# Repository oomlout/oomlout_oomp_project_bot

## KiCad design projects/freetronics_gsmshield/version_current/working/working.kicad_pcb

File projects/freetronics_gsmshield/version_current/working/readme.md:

# OOMP Project  
## GSMShield  by freetronics  
  
oomp key: oomp_projects_flat_freetronics_gsmshield  
(snippet of original readme)  

  full source readme at [readme_src.md](readme_src.md)  
  
source repo at: [https://github.com/freetronics/GSMShield](https://github.com/freetronics/GSMShield)  
## Board  

## Schematic  

[schematic pdf](working_schematic.pdf)  
## Images

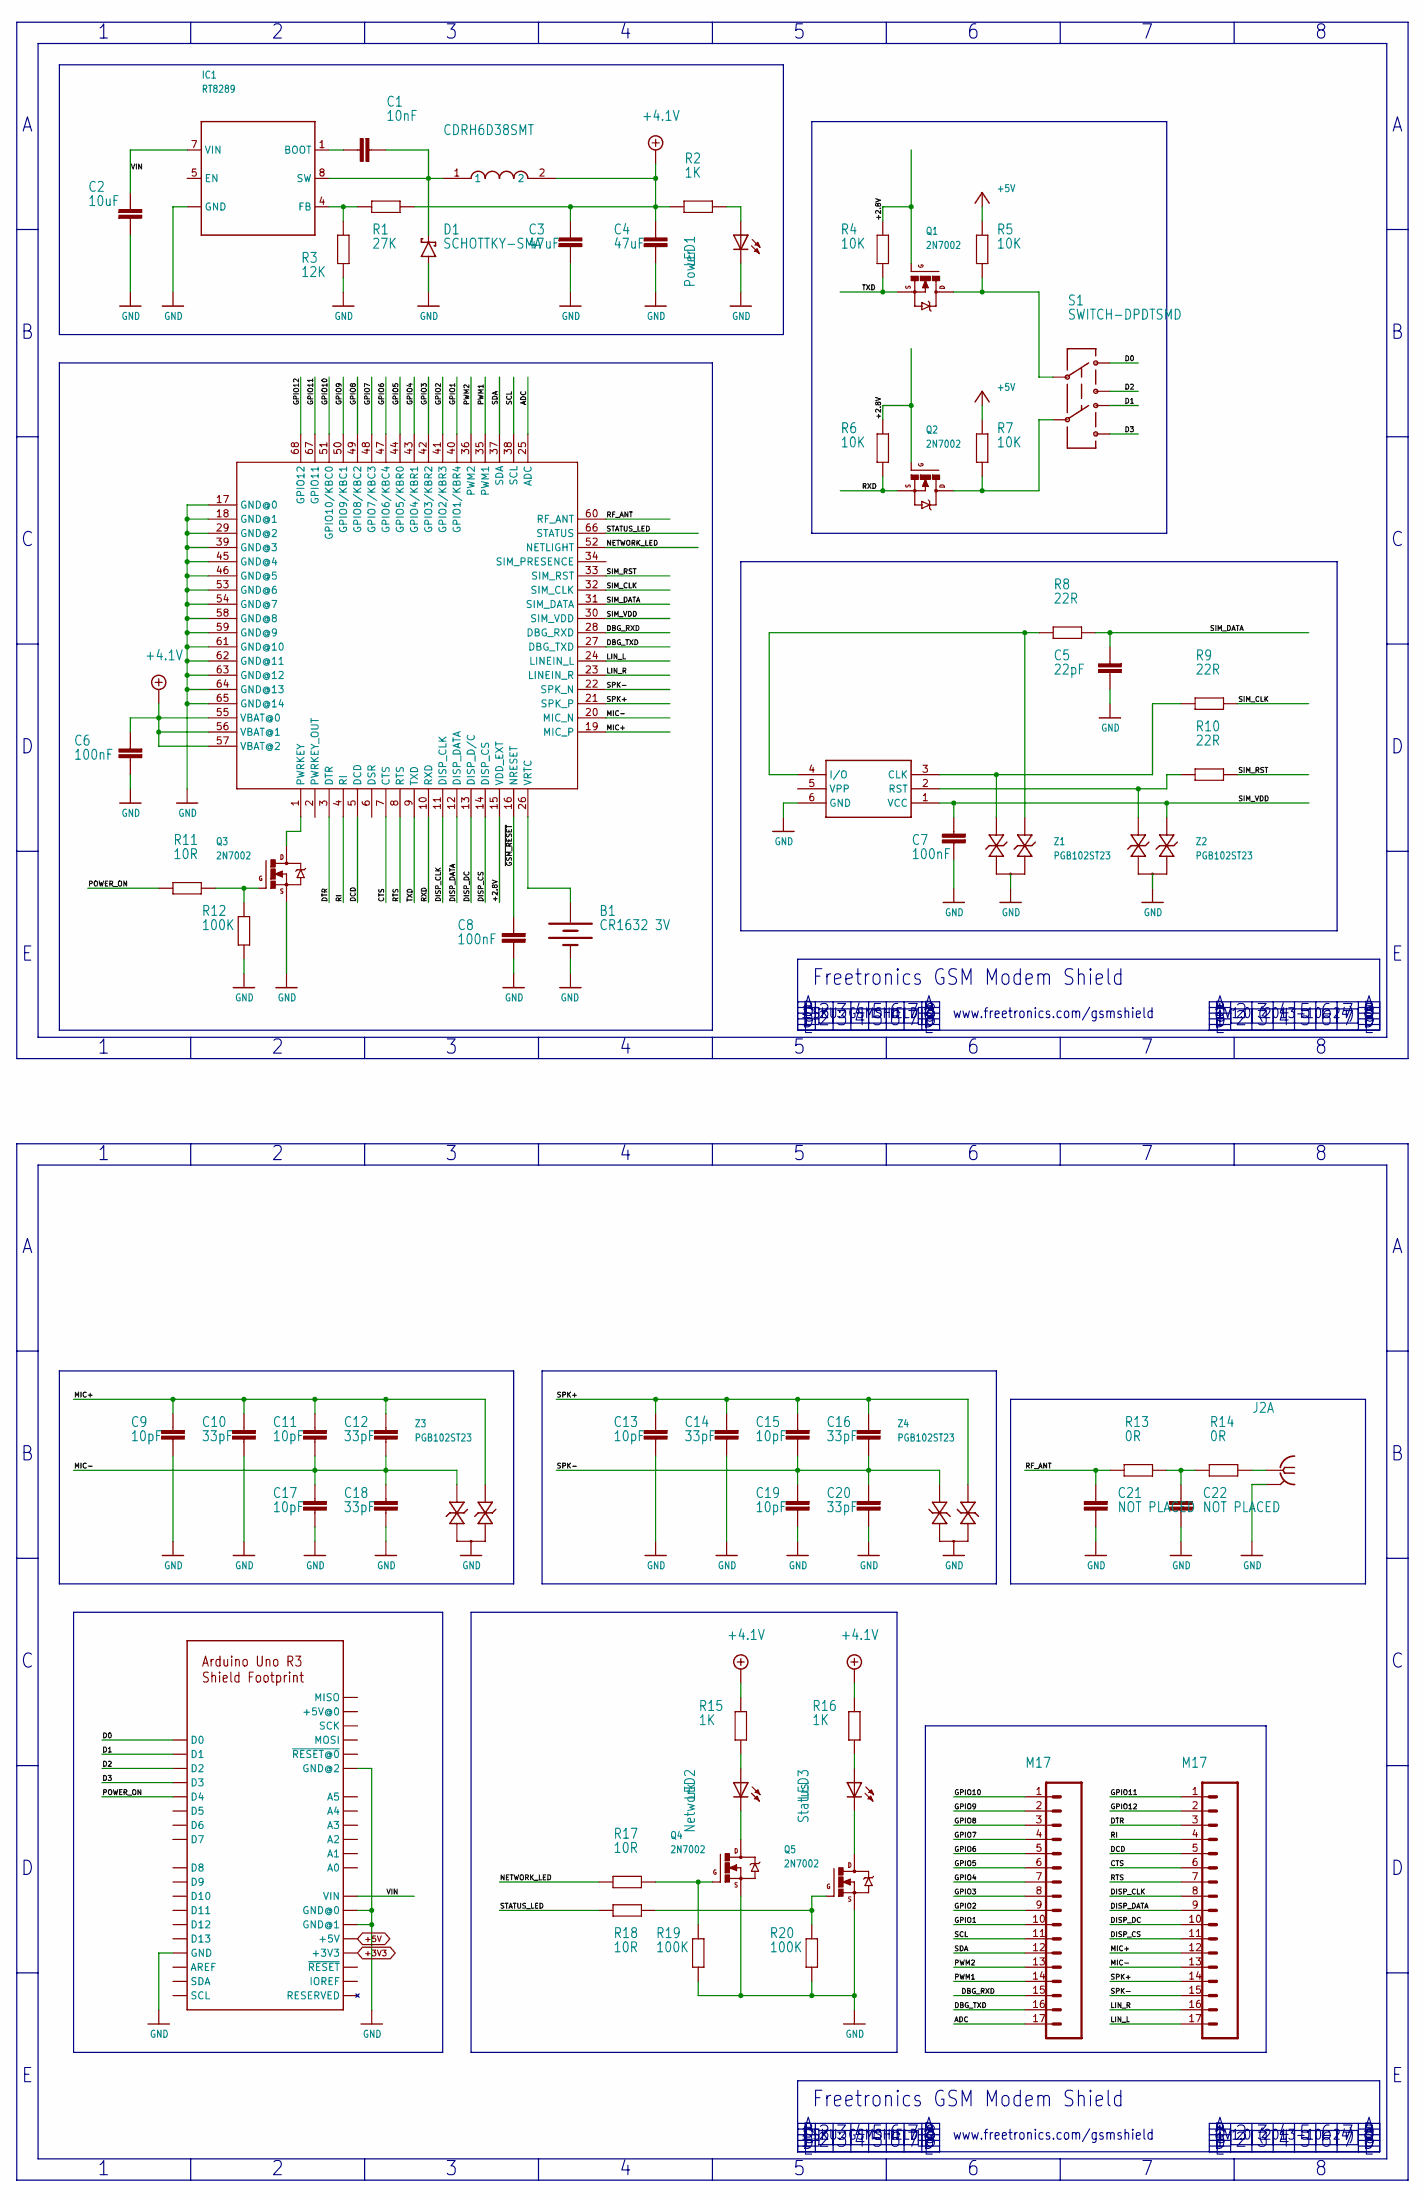
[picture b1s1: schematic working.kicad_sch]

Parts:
B1: CR1632 3V; BATCON_16MM
C1: 10nF; 0603
C2: 10uF; C1206; VOLTAGE 35V
C3, C4: 47uF; C1206; VOLTAGE 10V
C5: 22pF; 0603
C6, C7, C8: 100nF; 0603
C9, C11, C13, C15, C17, C19: 10pF; 0603
C10, C12, C14, C16, C18, C20: 33pF; 0603
C21, C22: NOT PLACED; C0402
D1: SCHOTTKY-SMA; SMA
IC1: RT8289; SO08T
IC2: SIM900
J1: SIMHOLDER3
J2: SMA-142-0701-881/886; J502-ND-142-0701-881_886
J3, J4: M17; 1X17
J5: ARDUINO-SHIELD_R3
L1: CDRH6D38SMT; CDRH
LED1: Power; LED-0603
LED2: Network; LED-0603
LED3: Status; LED-0603
Q1, Q2, Q3, Q4, Q5: 2N7002; SOT23-3
R1: 27K; 0603
R2, R15, R16: 1K; 0603
R3: 12K; 0603
R4, R5, R6, R7: 10K; 0603
R8, R9, R10: 22R; 0603
R11, R17, R18: 10R; 0603
R12, R19, R20: 100K; 0603
R13, R14: 0R; C0402
S1: SWITCH-DPDTSMD; AYZ0202
Z1, Z2, Z3, Z4: PGB102ST23; SOT23-3

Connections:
+2.8V: IC2.15 (VDD_EXT), Q1.1 (G), Q2.1 (G), R4.1, R6.1
+3V3: J5.3V3 (+3V3)
+4.0V: C3.1, C4.1, C6.2, IC2.55 (VBAT@0), IC2.56 (VBAT@1), IC2.57 (VBAT@2), L1.2, R1.1, R2.1, R15.1, R16.1
+5V: J5.+5V, R5.1, R7.1
ADC: IC2.25 (ADC), J3.17
CTS: IC2.7 (CTS), J4.6
D0: J5.D0, S1.1
D1: J5.D1, S1.4
D2: J5.D2, S1.3
D3: J5.D3, S1.6
DBG_RXD: IC2.28 (DBG_RXD), J3.15
DBG_TXD: IC2.27 (DBG_TXD), J3.16
DCD: IC2.5 (DCD), J4.5
DISP_CLK: IC2.11 (DISP_CLK), J4.8
DISP_CS: IC2.14 (DISP_CS), J4.11
DISP_DATA: IC2.12 (DISP_DATA), J4.9
DISP_DC: IC2.13 (DISP_D/C), J4.10
DTR: IC2.3 (DTR), J4.3
GND: B1.GND (-), C2.2, C3.2, C4.2, C5.1, C6.1, C7.1, C8.1, C9.1, C10.1, C13.1, C14.1, C17.1, C18.1, C19.1, C20.1, C21.1, C22.1, D1.A, IC1.2 (GND), IC1.3 (GND), IC1.6 (GND), IC1.PAD (GND), IC2.17 (GND@0), IC2.18 (GND@1), IC2.29 (GND@2), IC2.39 (GND@3), IC2.45 (GND@4), IC2.46 (GND@5), IC2.53 (GND@6), IC2.54 (GND@7), IC2.58 (GND@8), IC2.59 (GND@9), IC2.61 (GND@10), IC2.62 (GND@11), IC2.63 (GND@12), IC2.64 (GND@13), IC2.65 (GND@14), J1.6 (GND), J2.G@1 (GND), J2.G@2 (GND@1), J2.G@3 (GND@2), J2.G@4 (GND@3), J5.GND, J5.GND@0, J5.GND@1, J5.GND@2, LED1.C, Q3.2 (S), Q4.2 (S), Q5.2 (S), R3.1, R12.1, R19.1, R20.1, Z1.3, Z2.3, Z3.3, Z4.3
GPIO1: IC2.40 (GPIO1/KBR4), J3.10
GPIO2: IC2.41 (GPIO2/KBR3), J3.9
GPIO3: IC2.42 (GPIO3/KBR2), J3.8
GPIO4: IC2.43 (GPIO4/KBR1), J3.7
GPIO5: IC2.44 (GPIO5/KBR0), J3.6
GPIO6: IC2.47 (GPIO6/KBC4), J3.5
GPIO7: IC2.48 (GPIO7/KBC3), J3.4
GPIO8: IC2.49 (GPIO8/KBC2), J3.3
GPIO9: IC2.50 (GPIO9/KBC1), J3.2
GPIO10: IC2.51 (GPIO10/KBC0), J3.1
GPIO11: IC2.67 (GPIO11), J4.1
GPIO12: IC2.68 (GPIO12), J4.2
LIN_L: IC2.24 (LINEIN_L), J4.17
LIN_R: IC2.23 (LINEIN_R), J4.16
MIC+: C9.2, C10.2, C11.2, C12.2, IC2.19 (MIC_P), J4.12, Z3.2
MIC-: C11.1, C12.1, C17.2, C18.2, IC2.20 (MIC_N), J4.13, Z3.1
unnamed: LED1.A, R2.2
unnamed: LED2.C, Q4.3 (D)
unnamed: LED3.C, Q5.3 (D)
unnamed: Q4.1 (G), R17.1, R19.2
unnamed: Q5.1 (G), R18.1, R20.2
unnamed: B1.PWR@1 (+), IC2.26 (VRTC)
unnamed: J1.2 (RST), R10.2, Z2.1
unnamed: J1.3 (CLK), R9.2, Z1.1
unnamed: J1.4 (I/O), R8.2, Z1.2
unnamed: IC2.1 (PWRKEY), Q3.3 (D)
unnamed: Q3.1 (G), R11.1, R12.2
unnamed: C22.2, R13.2, R14.1
unnamed: J2.1, R14.2
unnamed: LED3.A, R16.2
unnamed: LED2.A, R15.2
unnamed: C1.1, D1.K, IC1.8 (SW), L1.1
unnamed: IC1.4 (FB), R1.2, R3.2
unnamed: C1.2, IC1.1 (BOOT)
NETWORK_LED: IC2.52 (NETLIGHT), R17.2
POWER_ON: J5.D4, R11.2
PWM1: IC2.35 (PWM1), J3.14
PWM2: IC2.36 (PWM2), J3.13
RF_ANT: C21.2, IC2.60 (RF_ANT), R13.1
RI: IC2.4 (RI), J4.4
RTS: IC2.8 (RTS), J4.7
RXD: IC2.10 (RXD), Q2.2 (S), R6.2
RXD_5V: Q2.3 (D), R7.2, S1.5
SCL: IC2.38 (SCL), J3.11
SDA: IC2.37 (SDA), J3.12
SIM_CLK: IC2.32 (SIM_CLK), R9.1
SIM_DATA: C5.2, IC2.31 (SIM_DATA), R8.1
SIM_RST: IC2.33 (SIM_RST), R10.1
SIM_VDD: C7.2, IC2.30 (SIM_VDD), J1.1 (VCC), Z2.2
SPK+: C13.2, C14.2, C15.2, C16.2, IC2.21 (SPK_P), J4.14, Z4.1
SPK-: C15.1, C16.1, C19.2, C20.2, IC2.22 (SPK_N), J4.15, Z4.2
STATUS_LED: IC2.66 (STATUS), R18.2
TXD: IC2.9 (TXD), Q1.2 (S), R4.2
TXD_5V: Q1.3 (D), R5.2, S1.2
VIN: C2.1, IC1.7 (VIN), J5.VIN
~GSM_RESET: C8.2, IC2.16 (NRESET)

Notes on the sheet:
www.freetronics.com/gsmshield
V1.0 (2013-10-24)
SKU: GSMSHIELD
Freetronics GSM Modem Shield

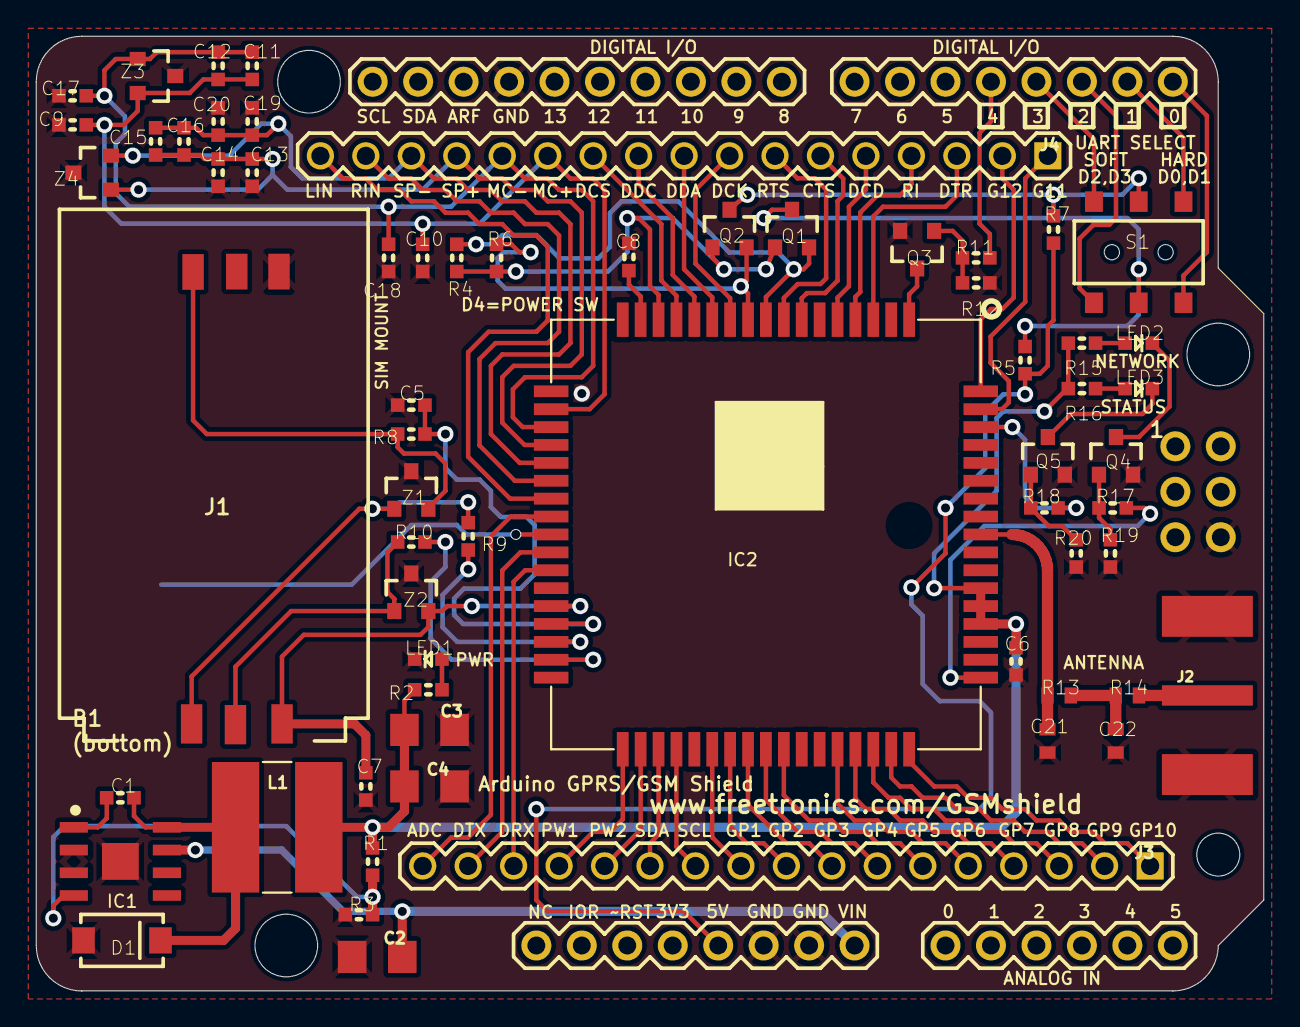
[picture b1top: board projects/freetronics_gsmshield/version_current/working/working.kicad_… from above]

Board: 2 copper layers, 68.6 x 53.3 mm, 65 parts (1 on the bottom side), 74 nets.

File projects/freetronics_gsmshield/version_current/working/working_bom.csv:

"Id";"Designator";"Footprint";"Quantity";"Designation";"Supplier and ref";
1;"R6,R7,R5,R4";"0603";4;"10K";;;
2;"R15,R2,R16";"0603";3;"1K";;;
3;"C1";"0603";1;"10nF";;;
4;"C10,C14,C16,C18,C12,C20";"0603";6;"33pF";;;
5;"J4";"1X17";1;"Breakout 2";;;
6;"R10,R8,R9";"0603";3;"22R";;;
7;"LED2";"LED-0603";1;"Network";;;
8;"J3";"1X17";1;"Breakout 1";;;
9;"R14,R13";"C0402";2;"0R";;;
10;"S1";"AYZ0202";1;"UART Select";;;
11;"J2";"J502-ND-142-0701-881_886";1;"Antenna";;;
12;"Q1,Q5,Q2,Q4,Q3";"SOT23-3";5;"2N7002";;;
13;"C13,C17,C9,C19,C15,C11";"0603";6;"10pF";;;
14;"Z4,Z2,Z3,Z1";"SOT23-3";4;"PGB102ST23";;;
15;"R20,R19,R12";"0603";3;"100K";;;
16;"C7,C8,C6";"0603";3;"100nF";;;
17;"C22,C21";"C0402";2;"NOT PLACED";;;
18;"L1";"CDRH";1;"10uH";;;
19;"C3,C4";"C1206";2;"47uF";;;
20;"R11,R17,R18";"0603";3;"10R";;;
21;"LED3";"LED-0603";1;"Status";;;
22;"LED1";"LED-0603";1;"Power";;;
23;"IC1";"SO08T";1;"RT8289";;;
24;"C5";"0603";1;"22pF";;;
25;"C2";"C1206";1;"10uF";;;
26;"D1";"SMA";1;"B340A-13-F";;;
27;"J5";"ARDUINO-SHIELD_R3";1;"ARDUINO-SHIELD_R3";;;
28;"R3";"0603";1;"12K";;;
29;"R1";"0603";1;"27K";;;
30;"IC2";"SIM900";1;"SIM900";;;
31;"J1";"SIMHOLDER3";1;"SIM Socket";;;
32;"B1";"BATCON_16MM";1;"CR1632 3V";;;

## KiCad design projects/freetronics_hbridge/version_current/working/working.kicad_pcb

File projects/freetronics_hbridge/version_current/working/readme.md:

# HBridge by freetronics  
This is a harvested standardized copy of a project from github.  
The original project can be found at:  
https://github.com/freetronics/HBridge  
Please consult that link for additional, details, files, and license information.  
Note: It was auto harvested and if the original repo had more than one board file or anything out of the ordinary the files here are likely not representative.

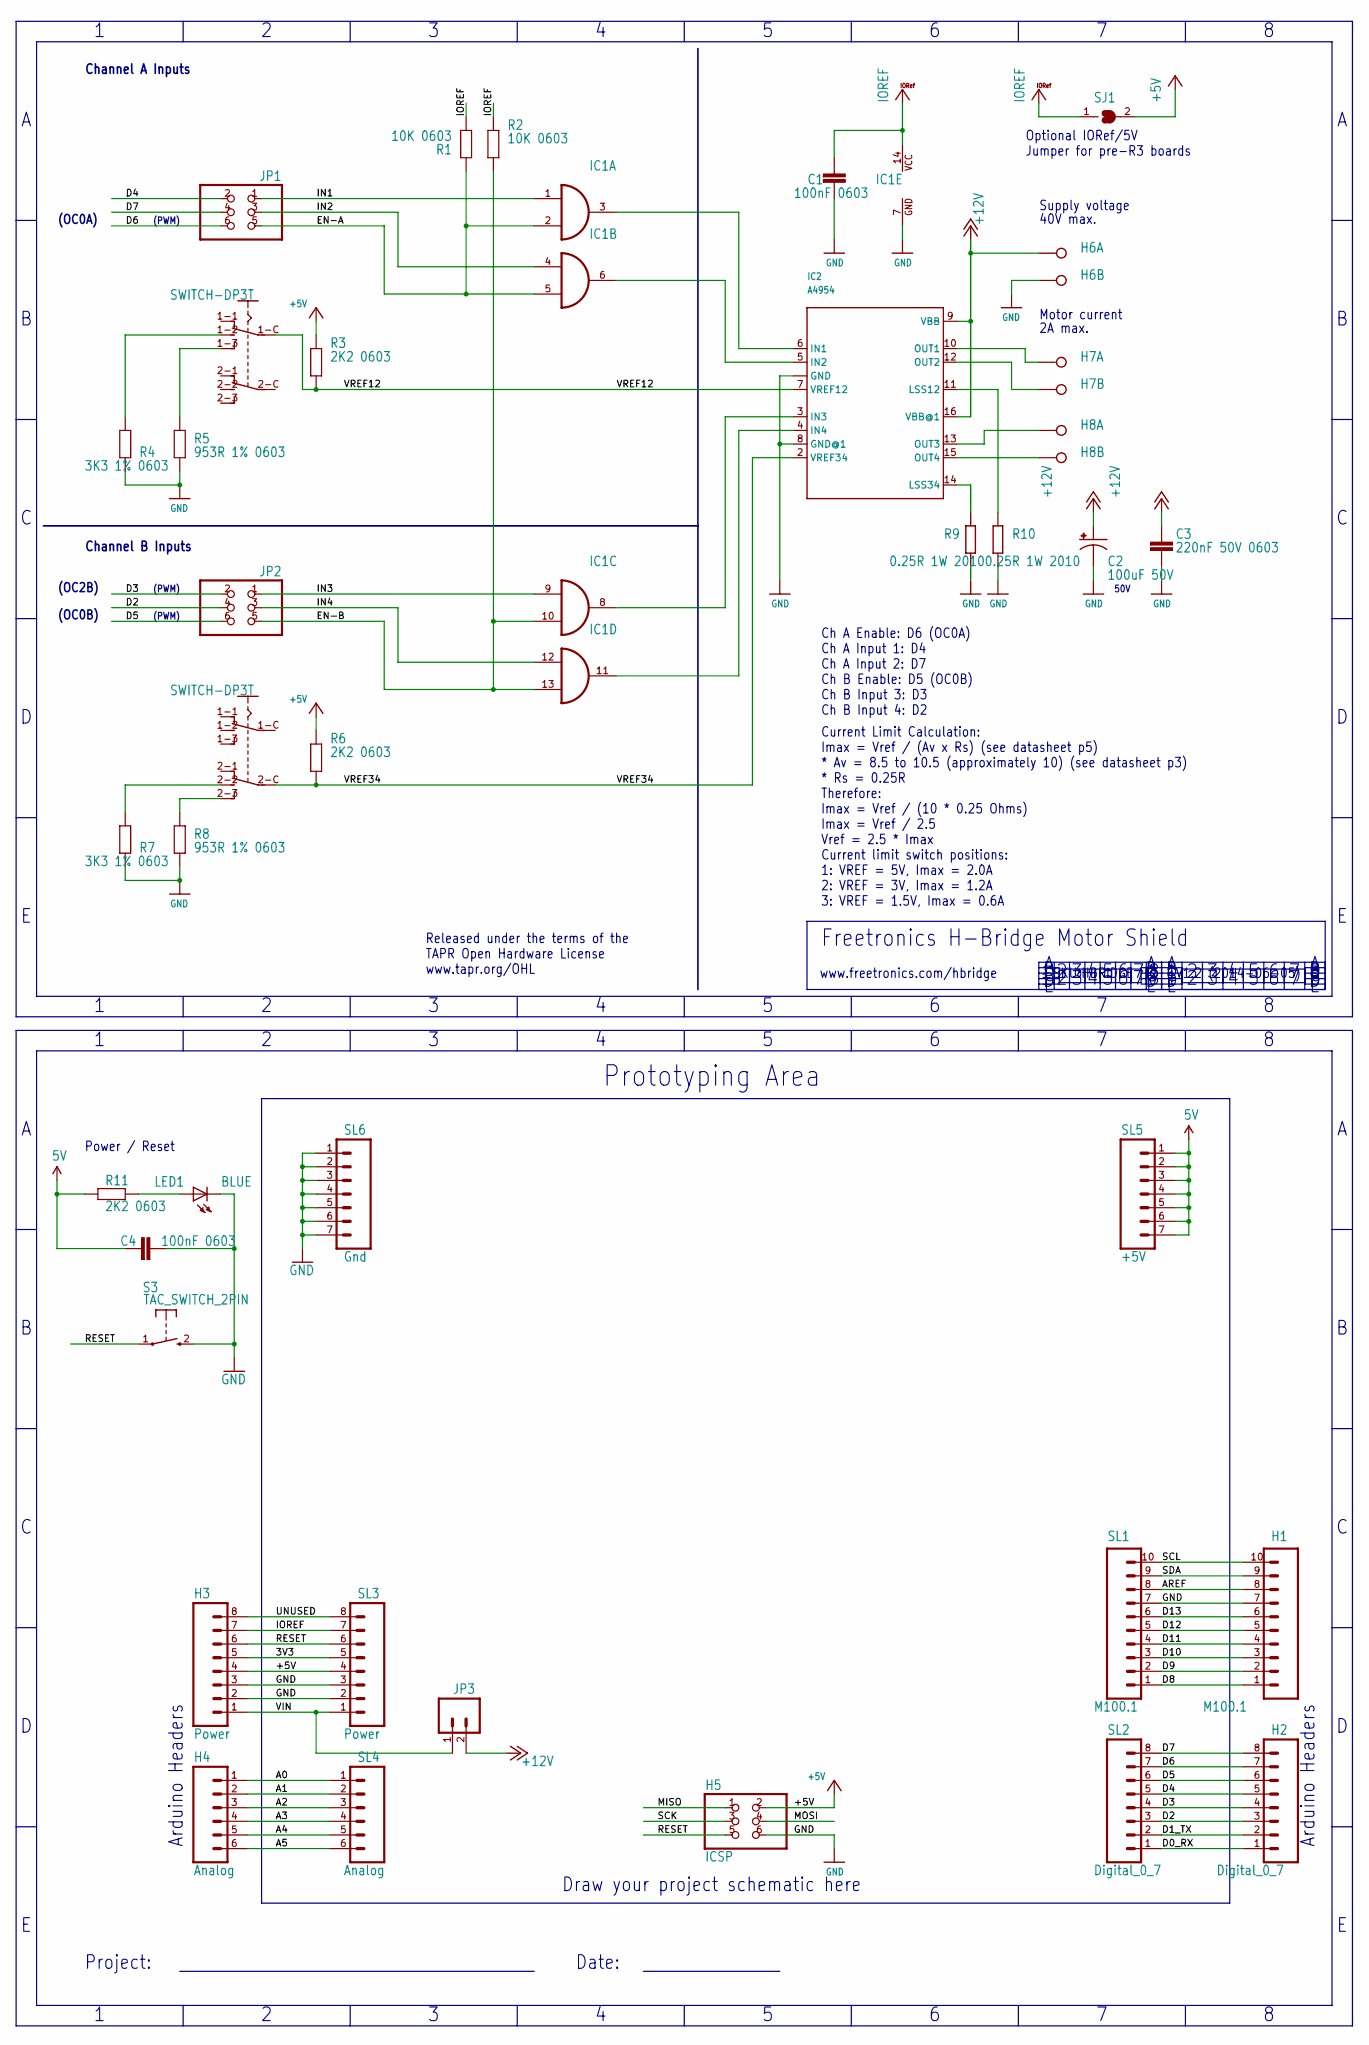
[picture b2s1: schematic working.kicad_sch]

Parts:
C1, C4: 100nF 0603; 0603
C2: 100uF 50V; PANASONIC_E
C3: 220nF 50V 0603; 0603
H1: M100.1; 1X10
H2: Digital_0_7; 1X08
H3: Power; 1X08
H4: Analog; 1X06
H5: ICSP; 2X03
H6: Power; W237-132
H7: Output A; W237-132
H8: Output B; W237-132
IC1: 7408D; SO14
IC2: A4954; TSSOP16-LP
JP1, JP2: PINHD-2X3; 2X03
JP3: M02PTH; 1X02
LED1: BLUE; LED-0603
R1, R2: 10K 0603; 0603
R3, R6, R11: 2K2 0603; 0603
R4, R7: 3K3 1% 0603; 0603
R5, R8: 953R 1% 0603; 0603
R9, R10: 0.25R 1W 2010; R2010
S1, S2: SWITCH-DP3T; MS-23C01
S3: TAC_SWITCH_2PIN; TACTILE_SWITCH_SMD_2PIN_TINY
SJ1: SJ
SL1: M100.1; 1X10
SL2: Digital_0_7; 1X08
SL3: Power; 1X08
SL4: Analog; 1X06
SL5: +5V; 1X07
SL6: Gnd; 1X07

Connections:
3V3: H3.5, SL3.5
A0: H4.1, SL4.1
A1: H4.2, SL4.2
A2: H4.3, SL4.3
A3: H4.4, SL4.4
A4: H4.5, SL4.5
A5: H4.6, SL4.6
AREF: H1.8, SL1.8
D0_RX: H2.1, SL2.1
D1_TX: H2.2, SL2.2
D2: H2.3, JP2.4, SL2.3
D3: H2.4, JP2.2, SL2.4
D4: H2.5, JP1.2, SL2.5
D5: H2.6, JP2.6, SL2.6
D6: H2.7, JP1.6, SL2.7
D7: H2.8, JP1.4, SL2.8
D8: H1.1, SL1.1
D9: H1.2, SL1.2
D10: H1.3, SL1.3
D11: H1.4, SL1.4
D12: H1.5, SL1.5
D13: H1.6, SL1.6
EN-A: IC1.2 (I1), IC1.5 (I1), JP1.5, R1.2
EN-B: IC1.10 (I1), IC1.13 (I1), JP2.5, R2.1
GND: C1.2, C2.-, C3.2, C4.2, H1.7, H3.2, H3.3, H5.6, H6.2, IC1.7 (GND), IC2.1 (GND), IC2.8 (GND@1), IC2.EXP (GND), LED1.C, R4.2, R5.2, R7.2, R8.2, R9.1, R10.1, S3.2 (S), SL1.7, SL3.2, SL3.3, SL6.1, SL6.2, SL6.3, SL6.4, SL6.5, SL6.6, SL6.7
IN1: IC1.1 (I0), JP1.1
IN2: IC1.4 (I0), JP1.3
IN3: IC1.9 (I0), JP2.1
IN4: IC1.12 (I0), JP2.3
IOREF: C1.1, H3.7, IC1.14 (VCC), R1.1, R2.2, SJ1.1, SL3.7
MISO: H5.1
MOSI: H5.4
unnamed: R8.1, S2.2-3
unnamed: IC1.11 (O), IC2.4 (IN4)
unnamed: IC1.8 (O), IC2.3 (IN3)
unnamed: IC1.6 (O), IC2.5 (IN2)
unnamed: IC1.3 (O), IC2.6 (IN1)
unnamed: H7.1, IC2.10 (OUT1)
unnamed: H7.2, IC2.12 (OUT2)
unnamed: H8.1, IC2.13 (OUT3)
unnamed: H8.2, IC2.15 (OUT4)
unnamed: IC2.14 (LSS34), R9.2
unnamed: IC2.11 (LSS12), R10.2
unnamed: R4.1, S1.1-2
unnamed: R5.1, S1.1-3
unnamed: LED1.A, R11.2
unnamed: R7.1, S2.2-2
RESET: H3.6, H5.5, S3.1, SL3.6
SCK: H5.3
SCL: H1.10, SL1.10
SDA: H1.9, SL1.9
UNUSED: H3.8, SL3.8
VBB: C2.+, C3.1, H6.1, IC2.9 (VBB), IC2.16 (VBB@1), JP3.2
VIN: H3.1, JP3.1, SL3.1
VREF12: IC2.7 (VREF12), R3.2, S1.1-C
VREF34: IC2.2 (VREF34), R6.2, S2.2-C

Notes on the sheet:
(OC0A)
2A max.
Optional IORef/5V Jumper for pre-R3 boards
40V max.
Date:
SKU:HBRIDGE
(PWM)
50V
Project:
Arduino Headers
V1.2 (2014-06-05)
Supply voltage
Channel B Inputs
Freetronics H-Bridge Motor Shield
Power / Reset
Channel A Inputs
(OC0B)
Draw your project schematic here
Prototyping Area
Current Limit Calculation: Imax = Vref / (Av x Rs) (see datasheet p5) * Av = 8.5 to 10.5 (approximately 10) (see datasheet p3) * Rs = 0.25R Therefore: Imax = Vref / (10 * 0.25 Ohms) Imax = Vref / 2.5 Vref = 2.5 * Imax Current limit switch positions: 1: VREF = 5V, Imax = 2.0A 2: VREF = 3V, Imax = 1.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
(OC2B)
www.freetronics.com/hbridge
Motor current
Released under the terms of the TAPR Open Hardware License www.tapr.org/OHL
Ch A Enable: D6 (OC0A) Ch A Input 1: D4 Ch A Input 2: D7 Ch B Enable: D5 (OC0B) Ch B Input 3: D3 Ch B Input 4: D2

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
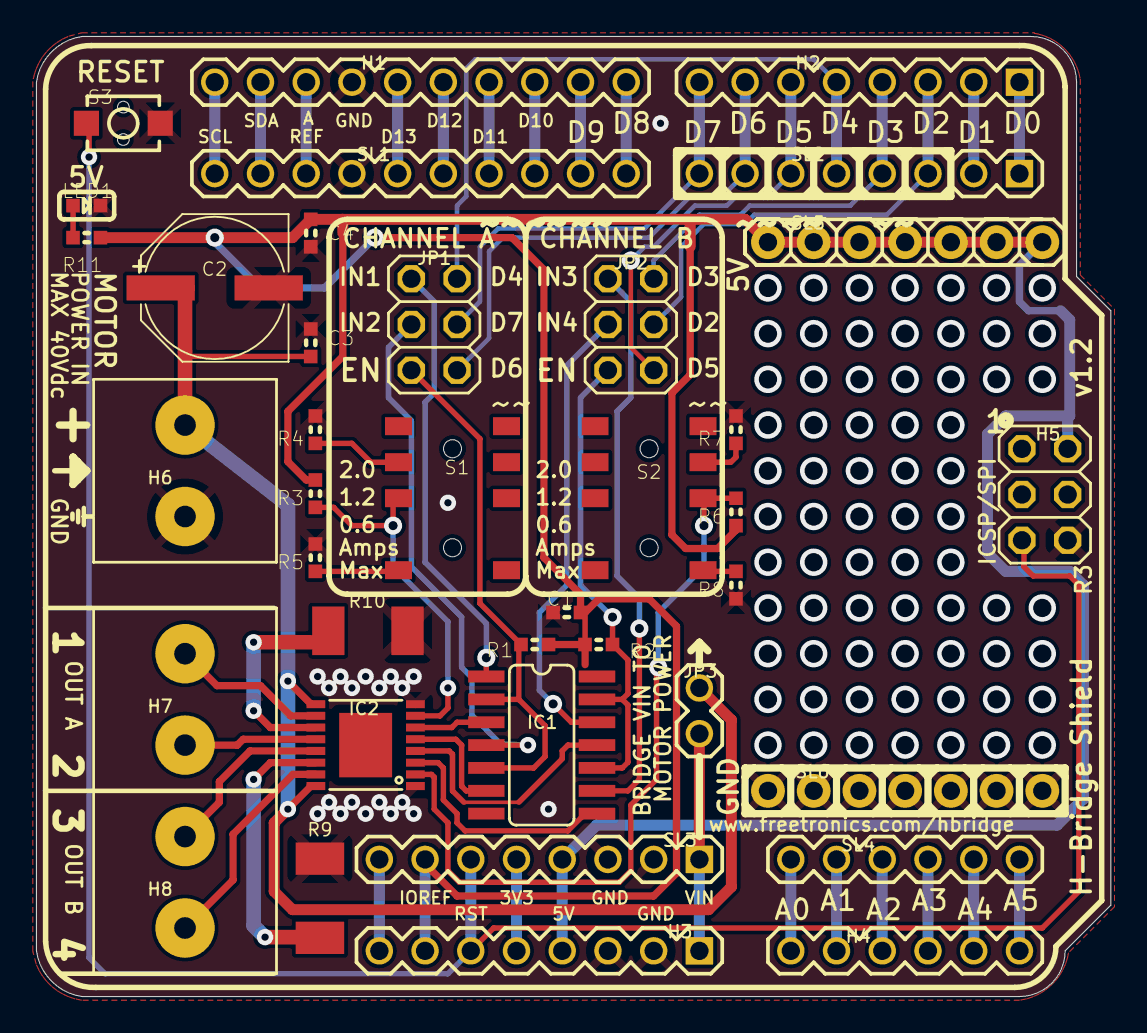
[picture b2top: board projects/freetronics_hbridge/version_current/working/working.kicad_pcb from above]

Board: 2 copper layers, 59.7 x 53.3 mm, 39 parts (1 on the bottom side), 54 nets.

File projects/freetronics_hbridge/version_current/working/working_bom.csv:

"Id";"Designator";"Footprint";"Quantity";"Designation";"Supplier and ref";
1;"R1,R2";"0603";2;"10K 0603";;;
2;"SL1,H1";"1X10";2;"Digital_8_13";;;
3;"H2,SL2";"1X08";2;"Digital_0_7";;;
4;"R5,R8";"0603";2;"953R 1% 0603";;;
5;"JP3";"1X02";1;"";;;
6;"H8";"W237-132";1;"Output B";;;
7;"R3,R6,R11";"0603";3;"2K2 0603";;;
8;"R4,R7";"0603";2;"3K3 1% 0603";;;
9;"C3";"0603";1;"220nF 50V 0603";;;
10;"C4,C1";"0603";2;"100nF 0603";;;
11;"R10,R9";"R2010";2;"0.25R 1W 2010";;;
12;"H5";"2X03";1;"ICSP";;;
13;"SL4,H4";"1X06";2;"Analog";;;
14;"H3,SL3";"1X08";2;"Power";;;
15;"H6";"W237-132";1;"Power";;;
16;"S1,S2";"MS-23C01";2;"SWITCH-DP3T MS-23C01";;;
17;"H7";"W237-132";1;"Output A";;;
18;"IC2";"TSSOP16-LP";1;"A4954 TSSOP-16";;;
19;"SL6";"1X07";1;"Gnd";;;
20;"LED1";"LED-0603";1;"BLUE";;;
21;"JP2,JP1";"2X03";2;"";;;
22;"S3";"TACTILE_SWITCH_SMD_2PIN_TINY";1;"RESET";;;
23;"SL5";"1X07";1;"+5V";;;
24;"IC1";"SO14";1;"74HC08D SOIC-14";;;
25;"C2";"PANASONIC_E";1;"100uF 50V";;;
26;"SJ1";"SJ";1;"";;;

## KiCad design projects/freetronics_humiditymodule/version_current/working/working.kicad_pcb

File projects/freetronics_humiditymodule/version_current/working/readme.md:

# HumidityModule by freetronics  
This is a harvested standardized copy of a project from github.  
The original project can be found at:  
https://github.com/freetronics/HumidityModule  
Please consult that link for additional, details, files, and license information.  
Note: It was auto harvested and if the original repo had more than one board file or anything out of the ordinary the files here are likely not representative.

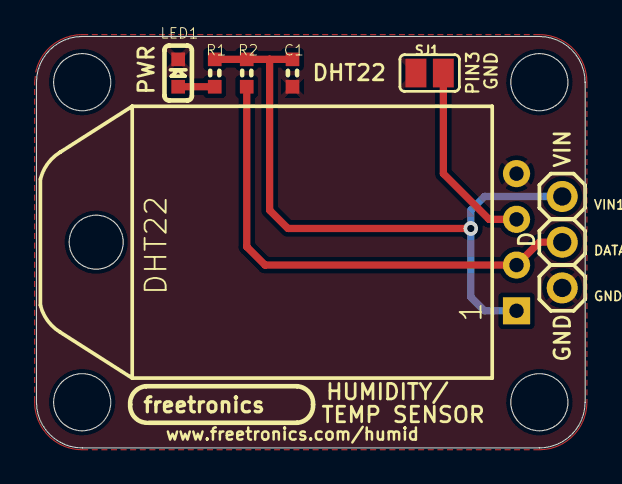
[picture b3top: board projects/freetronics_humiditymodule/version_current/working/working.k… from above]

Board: 2 copper layers, 30.5 x 22.9 mm, 13 parts (0 on the bottom side), 5 nets.

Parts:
@HOLE0, @HOLE1, @HOLE2, @HOLE3: (no value)
C1: 100nF; 0603
DATA1: M01PTH; 1X01
GND1: M01PTH; 1X01
IC1: DHT22FLAT; DHT22
LED1: POWER; LED-0603
R1: 1K; 0603
R2: 10K; 0603
SJ1: SJ
VIN1: M01PTH; 1X01

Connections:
DATA: DATA1.1, IC1.2, R2.2
GND: C1.2, GND1.1, IC1.4, LED1.C, SJ1.1
unnamed: LED1.A, R1.1
unnamed: IC1.3, SJ1.2
VIN: C1.1, IC1.1, R1.2, R2.1, VIN1.1

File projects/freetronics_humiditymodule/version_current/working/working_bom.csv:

"Id";"Designator";"Footprint";"Quantity";"Designation";"Supplier and ref";
1;"@HOLE3,@HOLE1,@HOLE2,@HOLE0";"";4;"";;;
2;"DATA1,VIN1,GND1";"1X01";3;"M01PTH";;;
3;"LED1";"LED-0603";1;"POWER";;;
4;"IC1";"DHT22";1;"DHT22FLAT";;;
5;"SJ1";"SJ";1;"";;;
6;"C1";"0603";1;"100nF";;;
7;"R2";"0603";1;"10K";;;
8;"R1";"0603";1;"1K";;;

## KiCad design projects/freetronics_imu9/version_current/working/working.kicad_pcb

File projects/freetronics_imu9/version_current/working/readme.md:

# IMU9 by freetronics  
This is a harvested standardized copy of a project from github.  
The original project can be found at:  
https://github.com/freetronics/IMU9  
Please consult that link for additional, details, files, and license information.  
Note: It was auto harvested and if the original repo had more than one board file or anything out of the ordinary the files here are likely not representative.

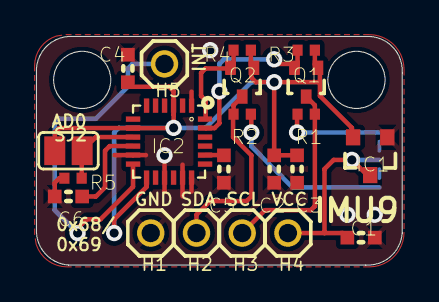
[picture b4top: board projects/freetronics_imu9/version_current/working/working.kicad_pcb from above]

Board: 2 copper layers, 20.3 x 12.7 mm, 24 parts (1 on the bottom side), 13 nets.

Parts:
@HOLE0, @HOLE1: (no value)
C1, C2: 1uF; 0603
C3, C6: 0.1uF; 0603
C4: 10nF; 0603
C5: 2.2nF; 0603
H1: GND; 1X01
H2: SDA; 1X01
H3: SCL; 1X01
H4: VCC; 1X01
H5: INT; 1X01
IC1: MCP1700T-3302E/TT; SOT23-3
IC2: MPU-9150; QFN-24MPU
Q1, Q2: RJU003N03 N-MOSFET; SOT32-3
R1, R2: 4K7 0402; 0402
R3, R4: 10K 0402; 0402
R5: 22K 0402; 0402
SJ1: SJ_2
SJ2: SJ

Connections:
3.3V: C2.1, C3.1, C4.1, IC1.2, IC2.3, IC2.8, IC2.13, Q1.1, Q2.1, R3.2, R4.2, SJ2.2
GND: C1.2, C2.2, C3.2, C4.2, C5.2, C6.1, H1.1, IC1.1, IC2.1, IC2.11, IC2.15, IC2.17, IC2.18, R5.1
unnamed: IC2.23, Q1.2, R3.1
unnamed: C5.1, IC2.20
unnamed: C1.1, H4.1, IC1.3, SJ1.2
unnamed: IC2.24, Q2.2, R4.1
unnamed: R1.2, SJ1.3
unnamed: R2.2, SJ1.1
unnamed: C6.2, IC2.10
unnamed: IC2.9, R5.2, SJ2.1
unnamed: H5.1, IC2.12
SCL: H3.1, Q1.3, R1.1
SDA: H2.1, Q2.3, R2.1

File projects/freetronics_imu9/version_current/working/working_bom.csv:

"Id";"Designator";"Footprint";"Quantity";"Designation";"Supplier and ref";
1;"IC1";"SOT23-3";1;"MCP1700T-3302E/TT";;;
2;"C2,C1";"0603";2;"1uF";;;
3;"@HOLE0,@HOLE1";"";2;"";;;
4;"H1";"1X01";1;"GND";;;
5;"IC2";"QFN-24MPU";1;"MPU-9150";;;
6;"C4";"0603";1;"10nF";;;
7;"H2";"1X01";1;"SDA";;;
8;"R4,R3";"0402";2;"10K 0402";;;
9;"R1,R2";"0402";2;"4K7 0402";;;
10;"Q1,Q2";"SOT32-3";2;"RJU003N03 N-MOSFET";;;
11;"H5";"1X01";1;"INT";;;
12;"C6,C3";"0603";2;"0.1uF";;;
13;"H4";"1X01";1;"VCC";;;
14;"C5";"0603";1;"2.2nF";;;
15;"R5";"0402";1;"22K 0402";;;
16;"SJ2";"SJ";1;"";;;
17;"H3";"1X01";1;"SCL";;;
18;"SJ1";"SJ_2";1;"";;;

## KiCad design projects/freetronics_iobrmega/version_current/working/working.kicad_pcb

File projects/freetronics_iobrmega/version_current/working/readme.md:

# IOBRMEGA by freetronics  
This is a harvested standardized copy of a project from github.  
The original project can be found at:  
https://github.com/freetronics/IOBRMEGA  
Please consult that link for additional, details, files, and license information.  
Note: It was auto harvested and if the original repo had more than one board file or anything out of the ordinary the files here are likely not representative.

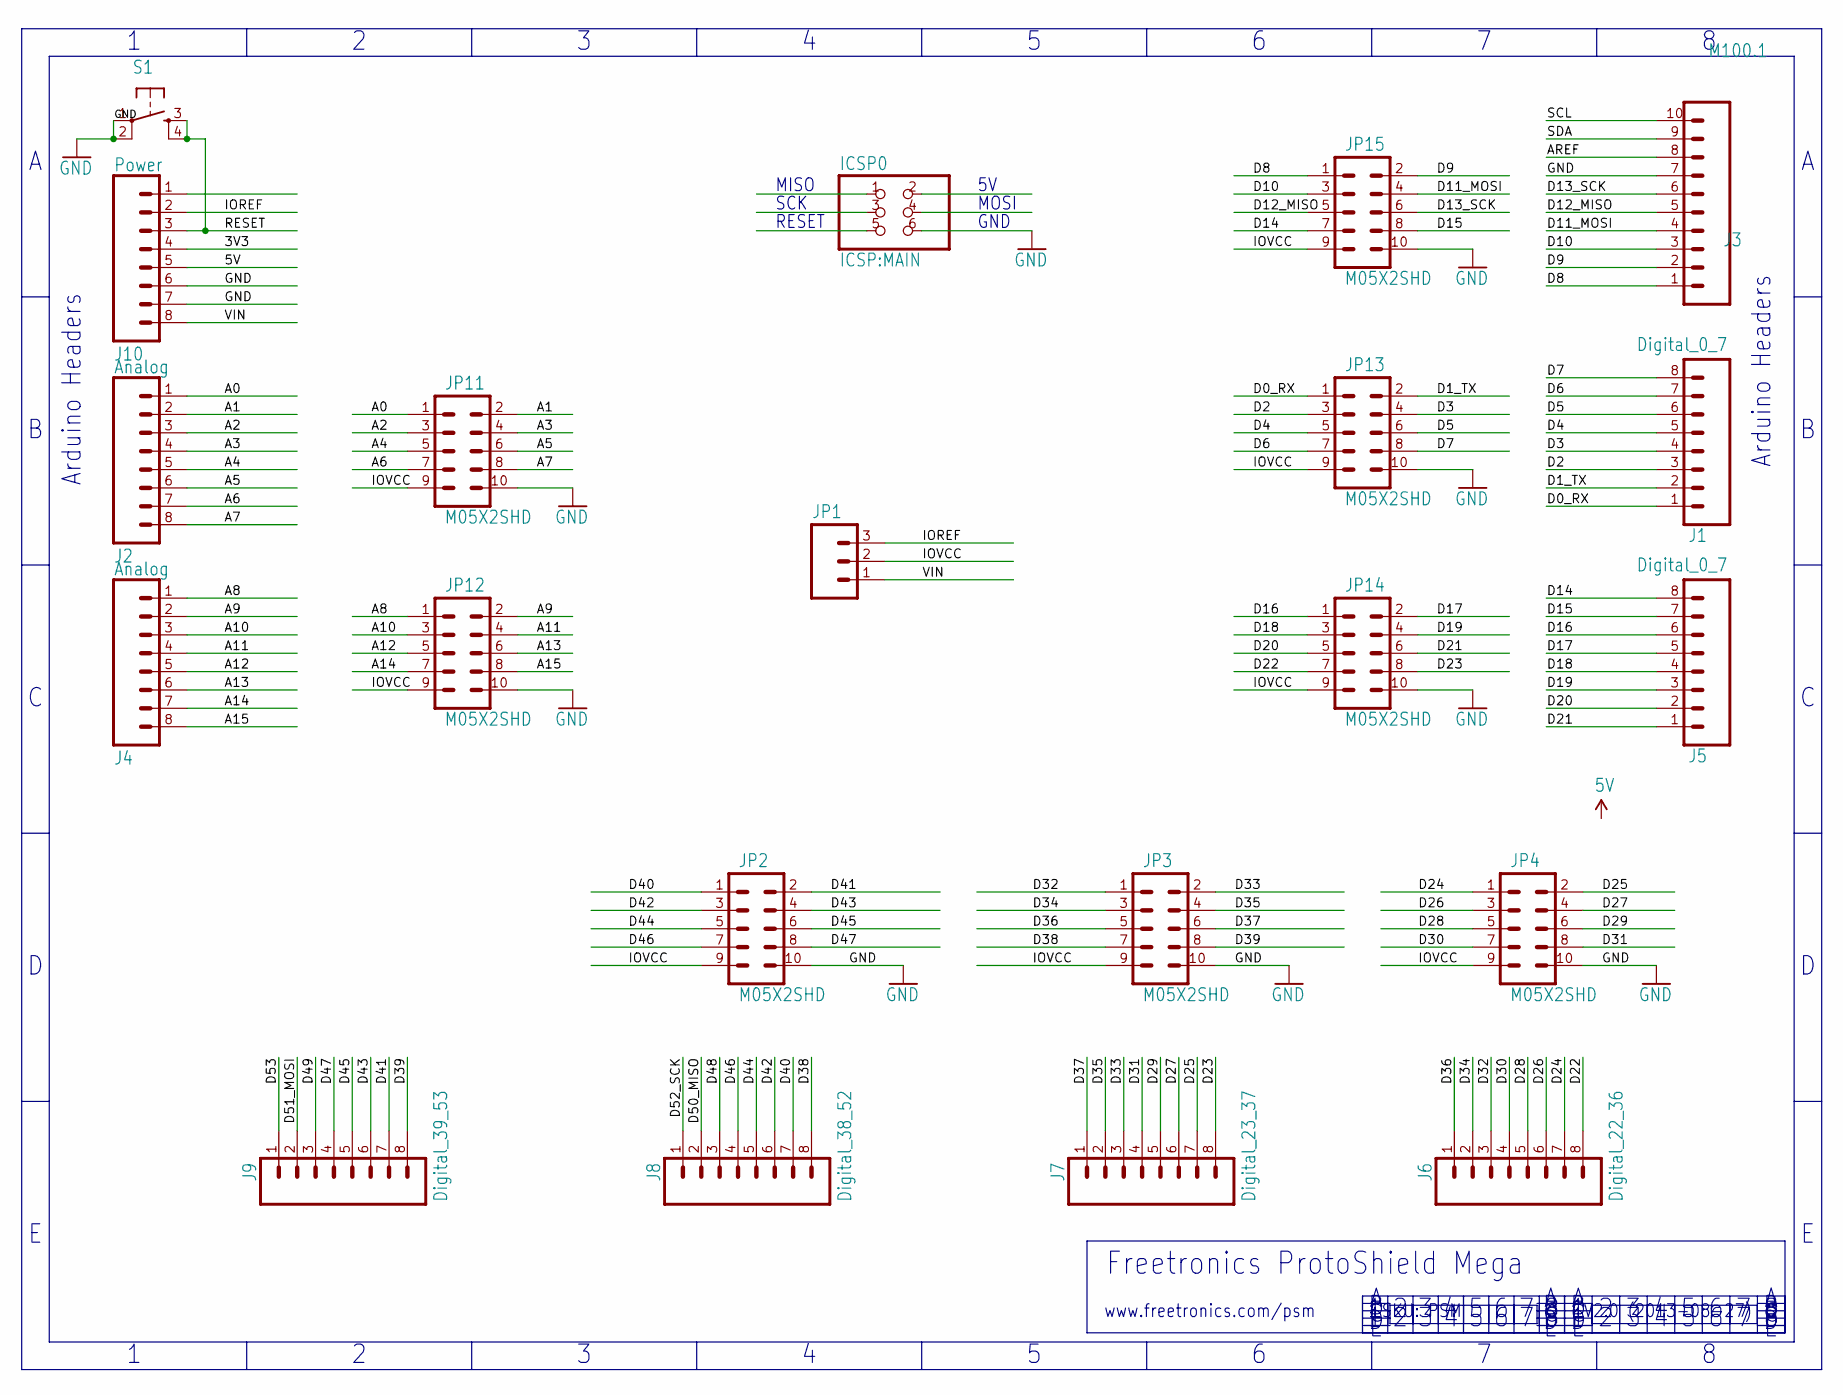
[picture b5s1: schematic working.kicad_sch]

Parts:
ICSP0: ICSP:MAIN; 2X03
J1, J5: Digital_0_7; 1X08
J2, J4: Analog; 1X08
J3: M100.1; 1X10
J6: Digital_22_36; 1X08
J7: Digital_23_37; 1X08
J8: Digital_38_52; 1X08
J9: Digital_39_53; 1X08
J10: Power; 1X08
JP1: M03PTH; 1X03
JP2, JP3, JP4, JP11, JP12, JP13, JP14, JP15: M05X2SHD; 2X5-SHROUDED
S1: TAC_SWITCHPTH; TACTILE-PTH

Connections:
3V3: J10.4
5V: J10.5
A0: J2.1, JP11.1
A1: J2.2, JP11.2
A2: J2.3, JP11.3
A3: J2.4, JP11.4
A4: J2.5, JP11.5
A5: J2.6, JP11.6
A6: J2.7, JP11.7
A7: J2.8, JP11.8
A8: J4.1, JP12.1
A9: J4.2, JP12.2
A10: J4.3, JP12.3
A11: J4.4, JP12.4
A12: J4.5, JP12.5
A13: J4.6, JP12.6
A14: J4.7, JP12.7
A15: J4.8, JP12.8
AREF: J3.8
D0_RX: J1.1, JP13.1
D1_TX: J1.2, JP13.2
D2: J1.3, JP13.3
D3: J1.4, JP13.4
D4: J1.5, JP13.5
D5: J1.6, JP13.6
D6: J1.7, JP13.7
D7: J1.8, JP13.8
D8: J3.1, JP15.1
D9: J3.2, JP15.2
D10: J3.3, JP15.3
D11_MOSI: J3.4, JP15.4
D12_MISO: J3.5, JP15.5
D13_SCK: J3.6, JP15.6
D14: J5.8, JP15.7
D15: J5.7, JP15.8
D16: J5.6, JP14.1
D17: J5.5, JP14.2
D18: J5.4, JP14.3
D19: J5.3, JP14.4
D20: J5.2, JP14.5
D21: J5.1, JP14.6
D22: J6.8, JP14.7
D23: J7.8, JP14.8
D24: J6.7, JP4.1
D25: J7.7, JP4.2
D26: J6.6, JP4.3
D27: J7.6, JP4.4
D28: J6.5, JP4.5
D29: J7.5, JP4.6
D30: J6.4, JP4.7
D31: J7.4, JP4.8
D32: J6.3, JP3.1
D33: J7.3, JP3.2
D34: J6.2, JP3.3
D35: J7.2, JP3.4
D36: J6.1, JP3.5
D37: J7.1, JP3.6
D38: J8.8, JP3.7
D39: J9.8, JP3.8
D40: J8.7, JP2.1
D41: J9.7, JP2.2
D42: J8.6, JP2.3
D43: J9.6, JP2.4
D44: J8.5, JP2.5
D45: J9.5, JP2.6
D46: J8.4, JP2.7
D47: J9.4, JP2.8
D48: J8.3
D49: J9.3
D50_MISO: J8.2
D51_MOSI: J9.2
D52_SCK: J8.1
D53: J9.1
GND: ICSP0.6, J3.7, J10.6, J10.7, JP2.10, JP3.10, JP4.10, JP11.10, JP12.10, JP13.10, JP14.10, JP15.10, S1.1, S1.2
IOREF: J10.2, JP1.3
IOVCC: JP1.2, JP2.9, JP3.9, JP4.9, JP11.9, JP12.9, JP13.9, JP14.9, JP15.9
RESET: J10.3, S1.3, S1.4
SCL: J3.10
SDA: J3.9
VIN: J10.8, JP1.1

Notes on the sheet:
Freetronics ProtoShield Mega
www.freetronics.com/psm
SCK
MISO
GND
Arduino Headers
RESET
MOSI
SKU: PSM
V2.0 (2013-08-27)

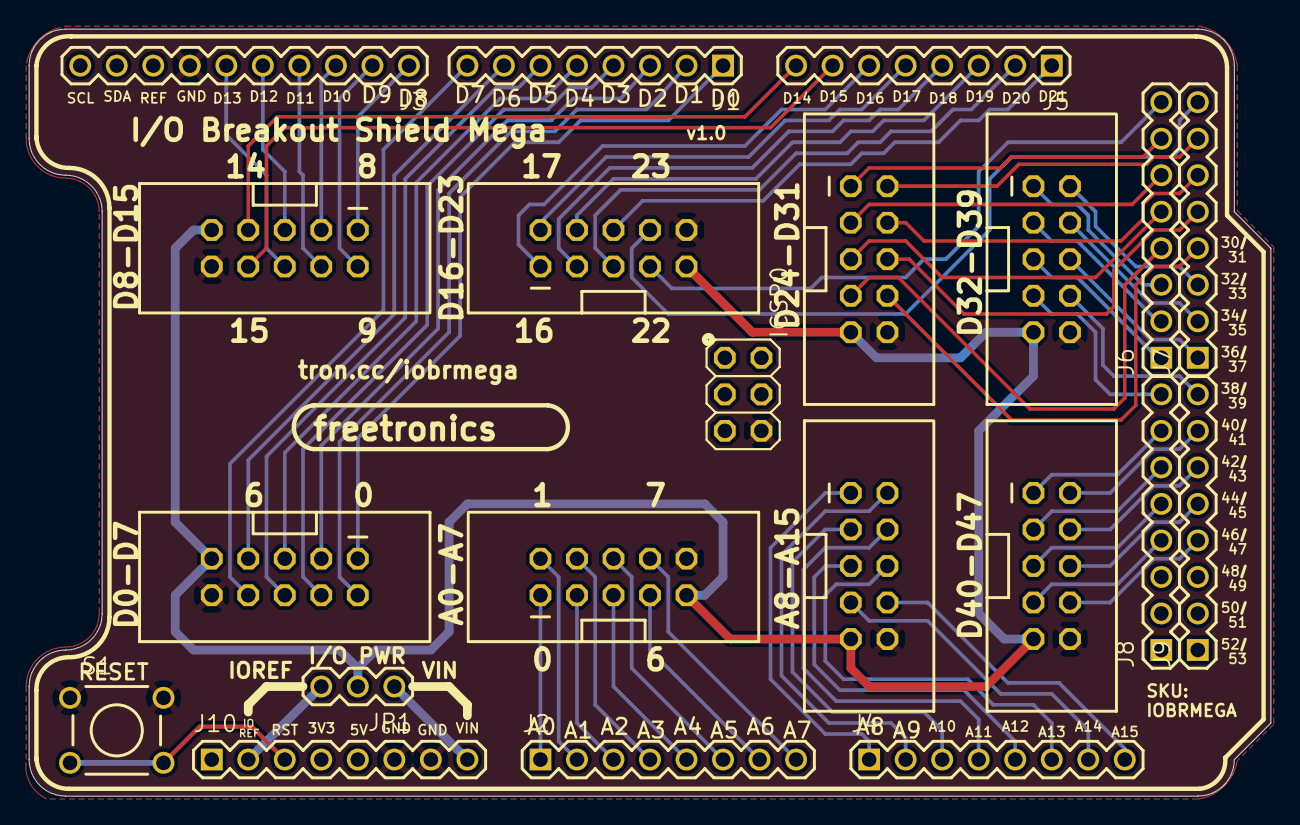
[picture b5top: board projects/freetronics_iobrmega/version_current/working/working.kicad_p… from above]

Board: 2 copper layers, 86.4 x 53.3 mm, 21 parts (0 on the bottom side), 69 nets.

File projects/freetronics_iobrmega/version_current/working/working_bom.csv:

"Id";"Designator";"Footprint";"Quantity";"Designation";"Supplier and ref";
1;"J4,J2";"1X08";2;"Analog";;;
2;"JP4,JP14,JP3,JP15,JP12,JP11,JP2,JP13";"2X5-SHROUDED";8;"M05X2SHD";;;
3;"J8";"1X08";1;"Digital_38_52";;;
4;"J9";"1X08";1;"Digital_39_53";;;
5;"J7";"1X08";1;"Digital_23_37";;;
6;"JP1";"1X03";1;"";;;
7;"S1";"TACTILE-PTH";1;"";;;
8;"J5,J1";"1X08";2;"Digital_0_7";;;
9;"J10";"1X08";1;"Power";;;
10;"ICSP0";"2X03";1;"ICSP:MAIN";;;
11;"J6";"1X08";1;"Digital_22_36";;;
12;"J3";"1X10";1;"Digital_8_13";;;

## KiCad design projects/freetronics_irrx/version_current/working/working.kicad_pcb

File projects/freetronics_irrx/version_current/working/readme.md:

# IRRX by freetronics  
This is a harvested standardized copy of a project from github.  
The original project can be found at:  
https://github.com/freetronics/IRRX  
Please consult that link for additional, details, files, and license information.  
Note: It was auto harvested and if the original repo had more than one board file or anything out of the ordinary the files here are likely not representative.

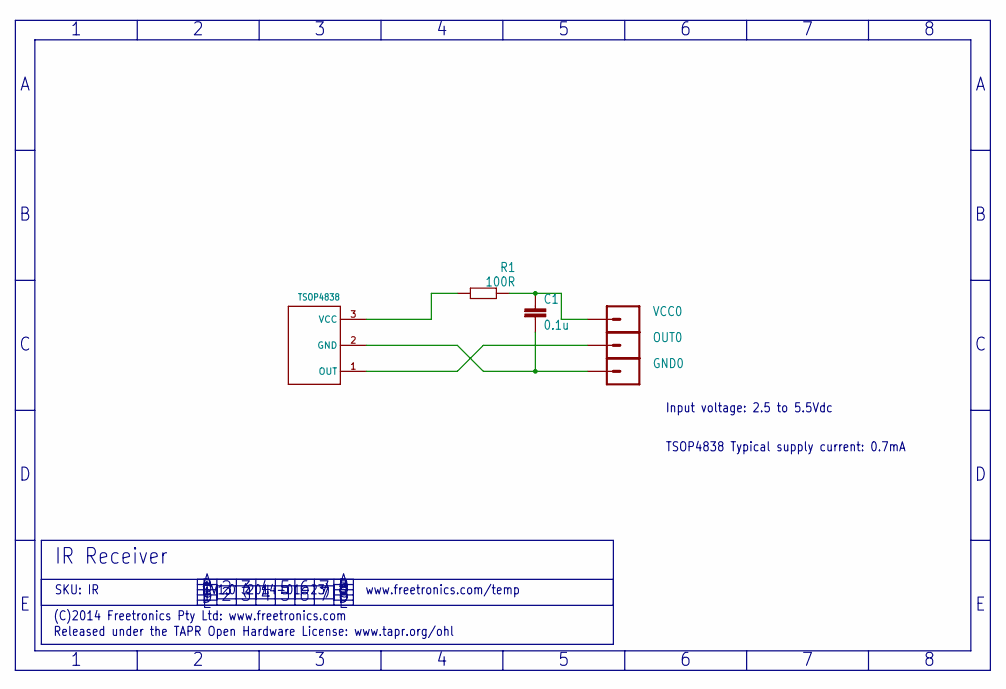
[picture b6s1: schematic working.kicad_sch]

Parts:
C1: 0.1u; 0603
GND0: M01PTH; 1X01
OUT0: M01PTH; 1X01
R1: 100R; 0603
TSOP4838: TSOP4838; TO220
VCC0: M01PTH; 1X01

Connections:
GND: C1.2, GND0.1, TSOP4838.2 (GND)
unnamed: OUT0.1, TSOP4838.1 (OUT)
unnamed: R1.2, TSOP4838.3 (VCC)
unnamed: C1.1, R1.1, VCC0.1

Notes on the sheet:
IR Receiver
TSOP4838 Typical supply current: 0.7mA
Input voltage: 2.5 to 5.5Vdc
V1.0 (2014-01-23)
SKU: IR
www.freetronics.com/temp
(C)2014 Freetronics Pty Ltd: www.freetronics.com
Released under the TAPR Open Hardware License: www.tapr.org/ohl

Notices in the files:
projects/freetronics_gsmshield/version_current/working/working.kicad_pcb:
Copyright 2013 Freetronics Pty Ltd
projects/freetronics_humiditymodule/version_current/working/working.kicad_pcb:
(C)2011 Freetronics
projects/freetronics_imu9/version_current/working/working.kicad_sch:
Copyright 2014 Freetronics Pty Ltd
projects/freetronics_kitten/version_current/working/working.kicad_pcb:
(C)2013 Freetronics Pty Ltd
